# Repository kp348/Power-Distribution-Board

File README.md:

## Overview

This project presents a **custom Power Distribution Board (PDB)** designed for **multirotor drones**.  
The board ensures reliable, efficient, and safe power management between the **battery**, **Motors**, **flight controller**, and **auxiliary modules** such as Workswell Camera, Doodle labs mesh radio, and Gremsy Gimbal.

The design prioritizes:
- Efficient DC-DC conversion
- Compact integration for UAV frames
- High current capacity and thermal stability
- Modular multi-voltage support (28 V, 22.2 V, 12 V, 5 V)

## Features
- **Input Voltage:** 48 V 
- **Power Outputs:**
  - 1x Motor Output (28 V / 5 A)
  - 1x Workswell Camera (22.2 V / 0.8108 A)
  - 1x Gremsy Gimbal (12 V / 4 A)
  - 1x Doodle labs mesh radio (5 V / 1 A)
  - 1x Flight Controller (5 V / 2.5 A)
- **Voltage Regulators:**
  - Buck converter : XL4015(28V , 12V rail) and LMR50410(22.2V and 5V rail)
- **Protection Features:**
  - Reverse polarity protection (MOSFET or diode)

## Components 

- XT60 Connector
- XL4015
- LMR50410
- Schottky Diode (1N5822)

## Schematic

## Functional Description

###  Input Stage
**Vin = 48 V** DC main bus  

### Output Stages
1. **U6 (XL4015)** → 48 V → 28 V @ 5 A  

2. **U4 (XL4015)** → 48 V → 12 V @ 4 A  

3. **U2 (LMR50410)** → 48 V → 22.2 V @ 0.8 A  

4. **U5 (LMR50410)** → 48 V → 5 V @ 2.5 A  

5. **U3 (LMR50410)** → 48 V → 5 V @ 1 A

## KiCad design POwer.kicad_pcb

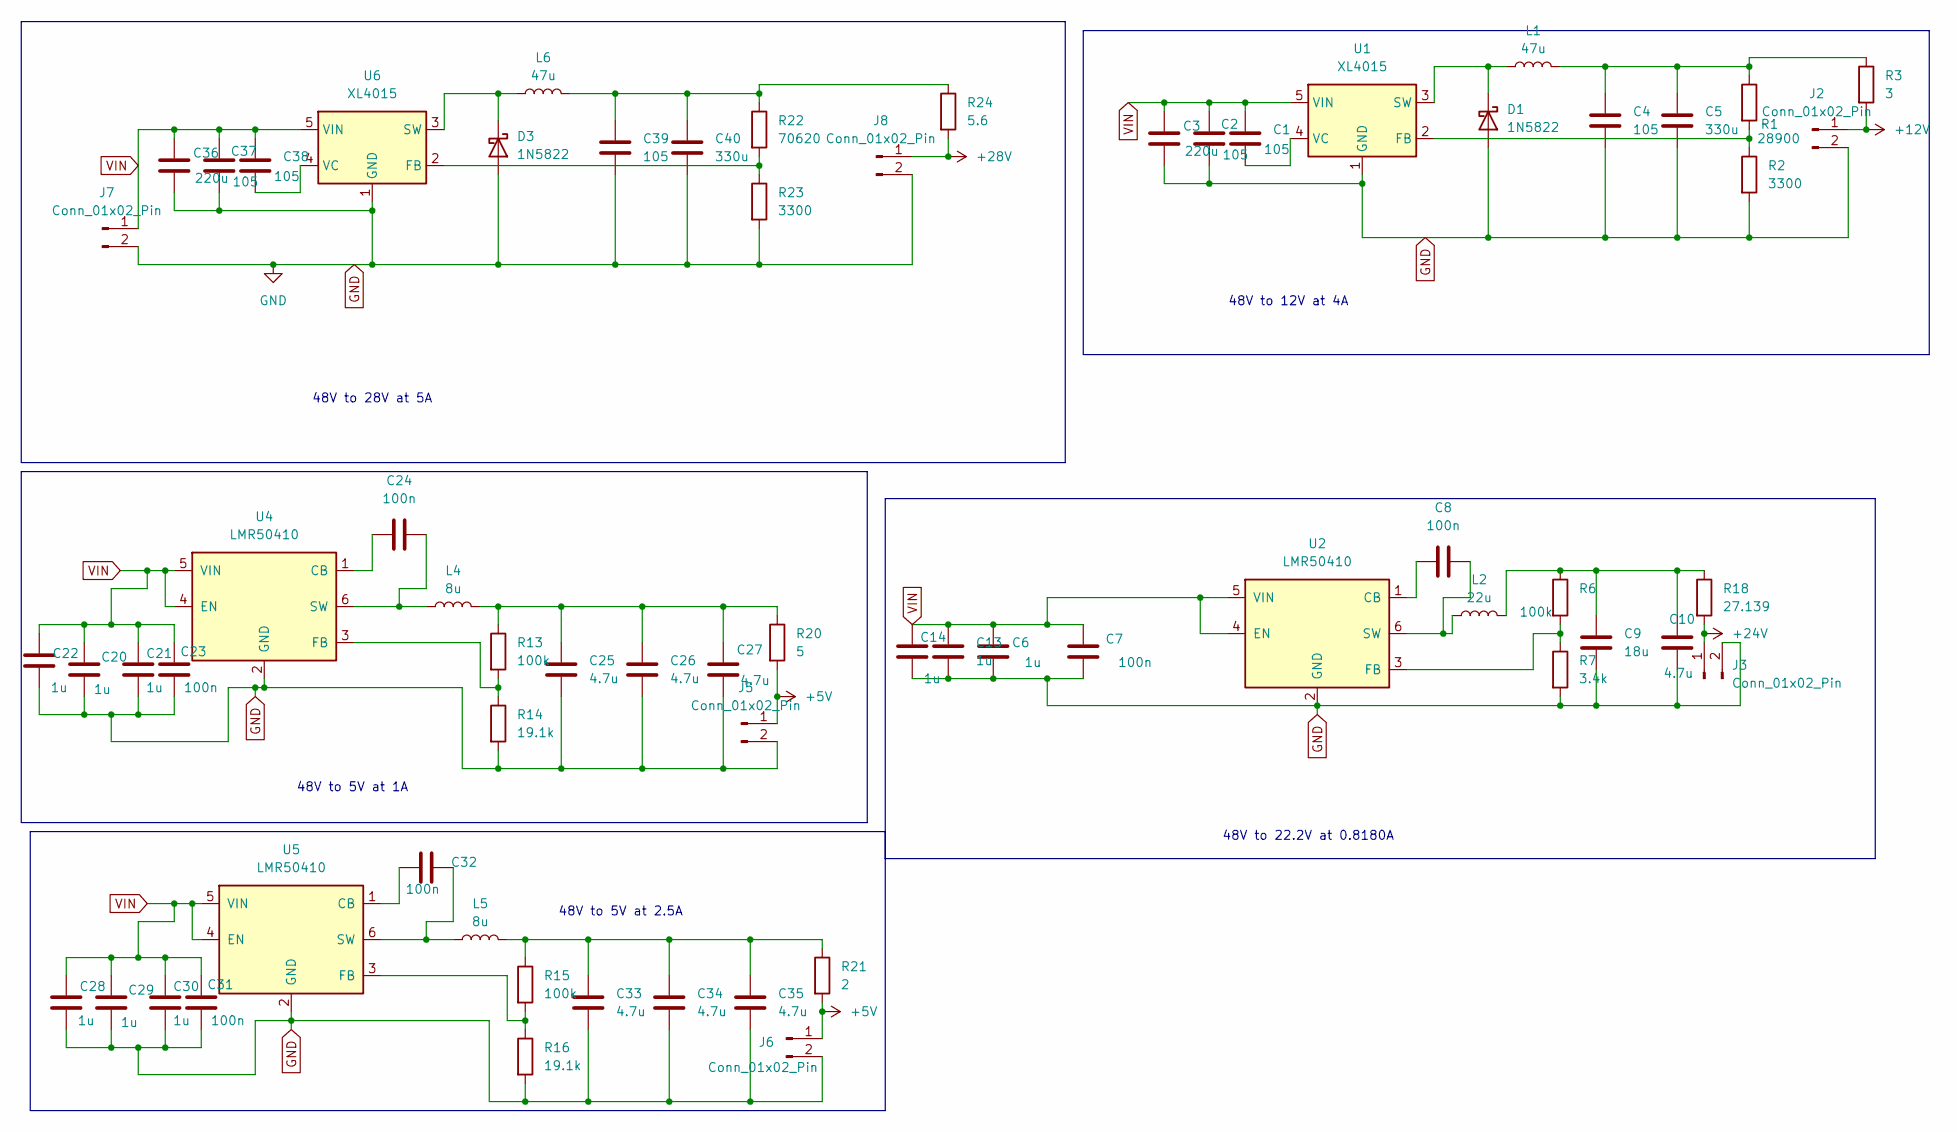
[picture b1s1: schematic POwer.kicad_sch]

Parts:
C1, C2, C4, C37, C38, C39: 105; C_0201_0603Metric_Pad0.64x0.40mm_HandSolder
C3, C36: 220u; C_0201_0603Metric_Pad0.64x0.40mm_HandSolder
C5, C40: 330u; C_0201_0603Metric_Pad0.64x0.40mm_HandSolder
C6, C13, C14, C20, C21, C22, C28, C29, C30: 1u; C_0201_0603Metric_Pad0.64x0.40mm_HandSolder
C7, C8, C23, C24, C31, C32: 100n; C_0201_0603Metric_Pad0.64x0.40mm_HandSolder
C9: 18u; C_0201_0603Metric_Pad0.64x0.40mm_HandSolder
C10, C25, C26, C27, C33, C34, C35: 4.7u; C_0201_0603Metric_Pad0.64x0.40mm_HandSolder
D1, D3: 1N5822; D_DO-201AD_P15.24mm_Horizontal
J2, J3, J5, J6, J7, J8: Conn_01x02_Pin; JST_EH_B2B-EH-A_1x02_P2.50mm_Vertical
L1, L6: 47u; L_0201_0603Metric_Pad0.64x0.40mm_HandSolder
L2: 22u; L_0201_0603Metric_Pad0.64x0.40mm_HandSolder
L4, L5: 8u; L_0201_0603Metric_Pad0.64x0.40mm_HandSolder
R1: 28900; R_0201_0603Metric_Pad0.64x0.40mm_HandSolder
R2, R23: 3300; R_0201_0603Metric_Pad0.64x0.40mm_HandSolder
R3: 3; R_0201_0603Metric_Pad0.64x0.40mm_HandSolder
R6, R13, R15: 100k; R_0201_0603Metric_Pad0.64x0.40mm_HandSolder
R7: 3.4k; R_0201_0603Metric_Pad0.64x0.40mm_HandSolder
R14, R16: 19.1k; R_0201_0603Metric_Pad0.64x0.40mm_HandSolder
R18: 27.139; R_0201_0603Metric_Pad0.64x0.40mm_HandSolder
R20: 5; R_0201_0603Metric_Pad0.64x0.40mm_HandSolder
R21: 2; R_0201_0603Metric_Pad0.64x0.40mm_HandSolder
R22: 70620; R_0201_0603Metric_Pad0.64x0.40mm_HandSolder
R24: 5.6; R_0201_0603Metric_Pad0.64x0.40mm_HandSolder
U1, U6: XL4015; TO-263-5_TabPin3
U2, U4, U5: LMR50410; SOT-23-6

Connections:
+5V: J5.1, J6.1, R20.2, R21.2
+12V: J2.1, R3.2
+24V: J3.1, R18.2
+28V: J8.1, R24.2
GND: C2.2, C3.2, C4.2, C5.2, C6.2, C7.2, C9.1, C10.1, C13.2, C14.2, C20.2, C21.2, C22.2, C23.2, C25.2, C26.2, C27.2, C28.2, C29.2, C30.2, C31.2, C33.2, C34.2, C35.2, C36.2, C37.2, C39.2, C40.2, D1.2 (A), D3.2 (A), J2.2, J3.2, J5.2, J6.2, J7.2, J8.2, R2.2, R7.2, R14.2, R16.2, R23.2, U1.1 (GND), U2.2 (GND), U4.2 (GND), U5.2 (GND), U6.1 (GND)
unnamed: C4.1, C5.1, L1.2, R1.1, R3.1
unnamed: C9.2, C10.2, L2.2, R6.1, R18.1
unnamed: C25.1, C26.1, C27.1, L4.2, R13.1, R20.1
unnamed: C33.1, C34.1, C35.1, L5.2, R15.1, R21.1
unnamed: C39.1, C40.1, L6.2, R22.1, R24.1
unnamed: D1.1 (K), L1.1, U1.3 (SW)
unnamed: D3.1 (K), L6.1, U6.3 (SW)
unnamed: R1.2, R2.1, U1.2 (FB)
unnamed: C1.2, U1.4 (VC)
unnamed: C8.1, U2.1 (CB)
unnamed: R6.2, R7.1, U2.3 (FB)
unnamed: C8.2, L2.1, U2.6 (SW)
unnamed: C24.1, U4.1 (CB)
unnamed: R13.2, R14.1, U4.3 (FB)
unnamed: C24.2, L4.1, U4.6 (SW)
unnamed: C32.1, U5.1 (CB)
unnamed: R15.2, R16.1, U5.3 (FB)
unnamed: C32.2, L5.1, U5.6 (SW)
unnamed: R22.2, R23.1, U6.2 (FB)
unnamed: C38.2, U6.4 (VC)
VIN: C1.1, C2.1, C3.1, C6.1, C7.1, C13.1, C14.1, C20.1, C21.1, C22.1, C23.1, C28.1, C29.1, C30.1, C31.1, C36.1, C37.1, C38.1, J7.1, U1.5 (VIN), U2.4 (EN), U2.5 (VIN), U4.4 (EN), U4.5 (VIN), U5.4 (EN), U5.5 (VIN), U6.5 (VIN)

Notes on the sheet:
48V to 12V at 4A
48V to 22.2V at 0.8180A
48V to 5V at 1A
48V to 28V at 5A
48V to 5V at 2.5A

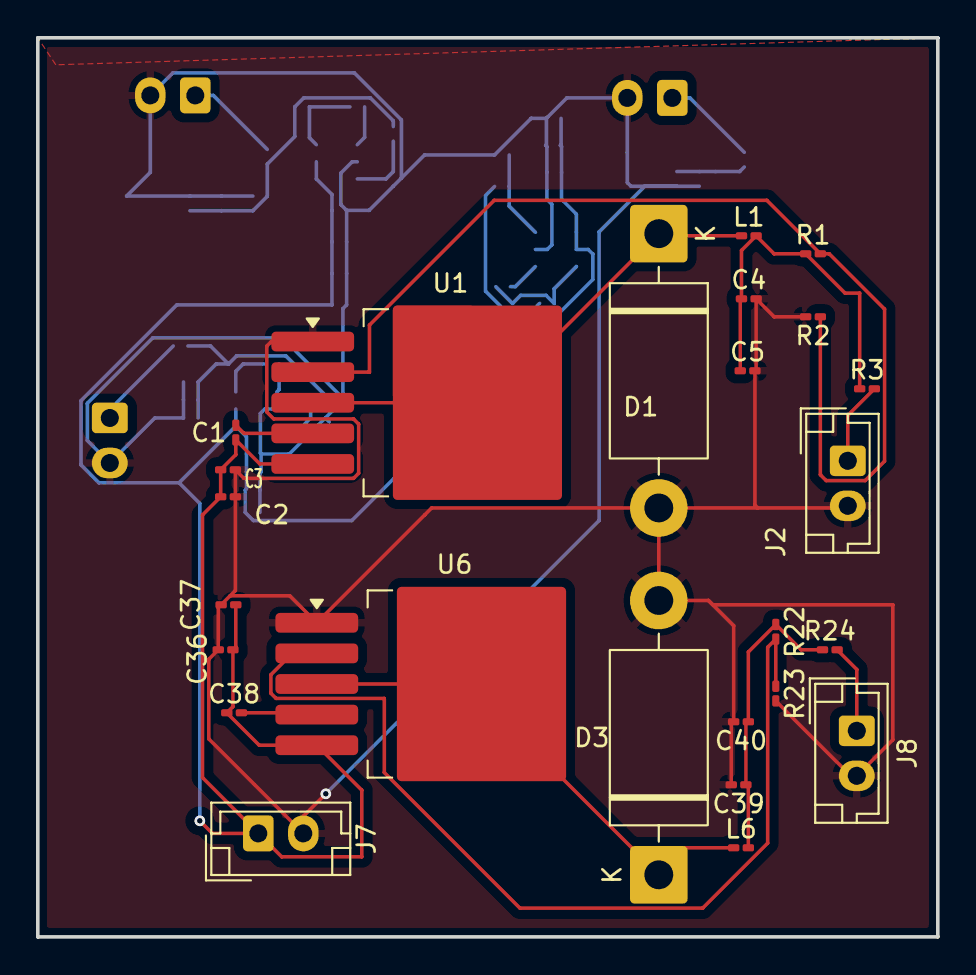
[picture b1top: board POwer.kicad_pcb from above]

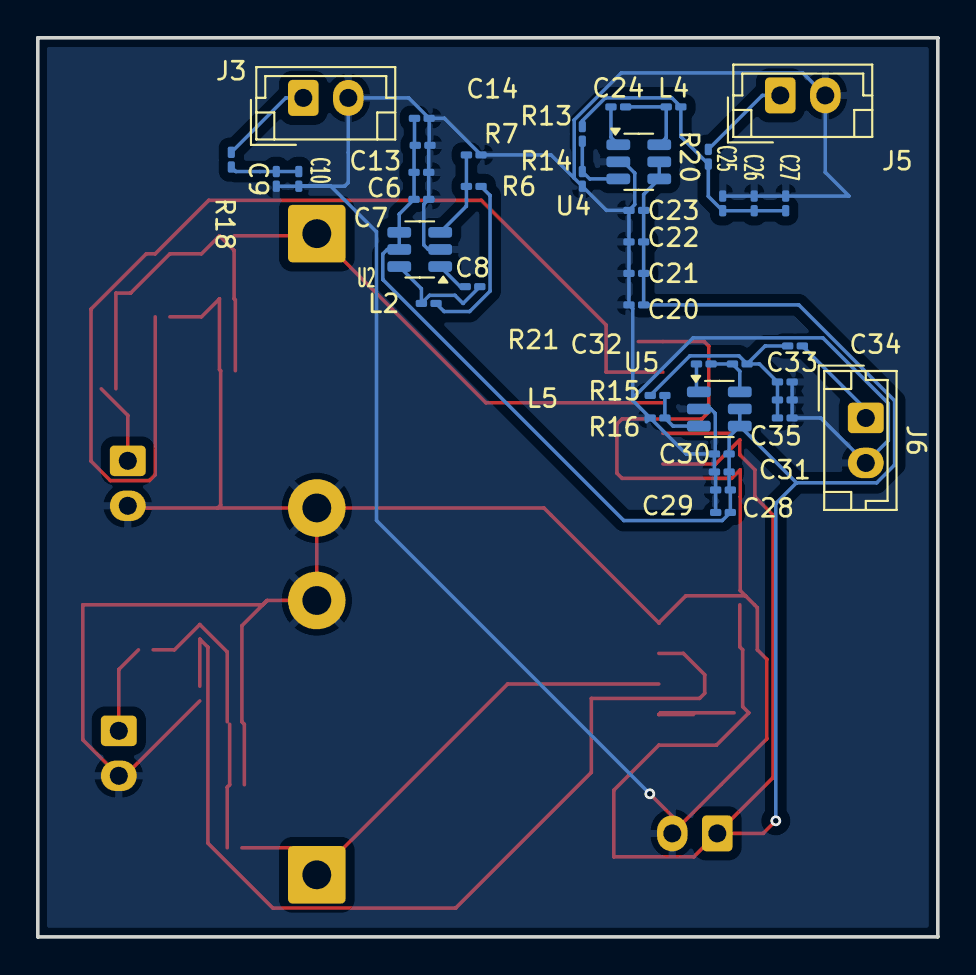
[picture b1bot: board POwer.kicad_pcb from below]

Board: 2 copper layers, 50.0 x 49.9 mm, 66 parts (41 on the bottom side), 26 nets.
